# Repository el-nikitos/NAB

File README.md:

NAB

NAB_A - измерительный модуль-передатчик
NAB_B - модуль отображение-приемник
NAB_C - зарядная станция

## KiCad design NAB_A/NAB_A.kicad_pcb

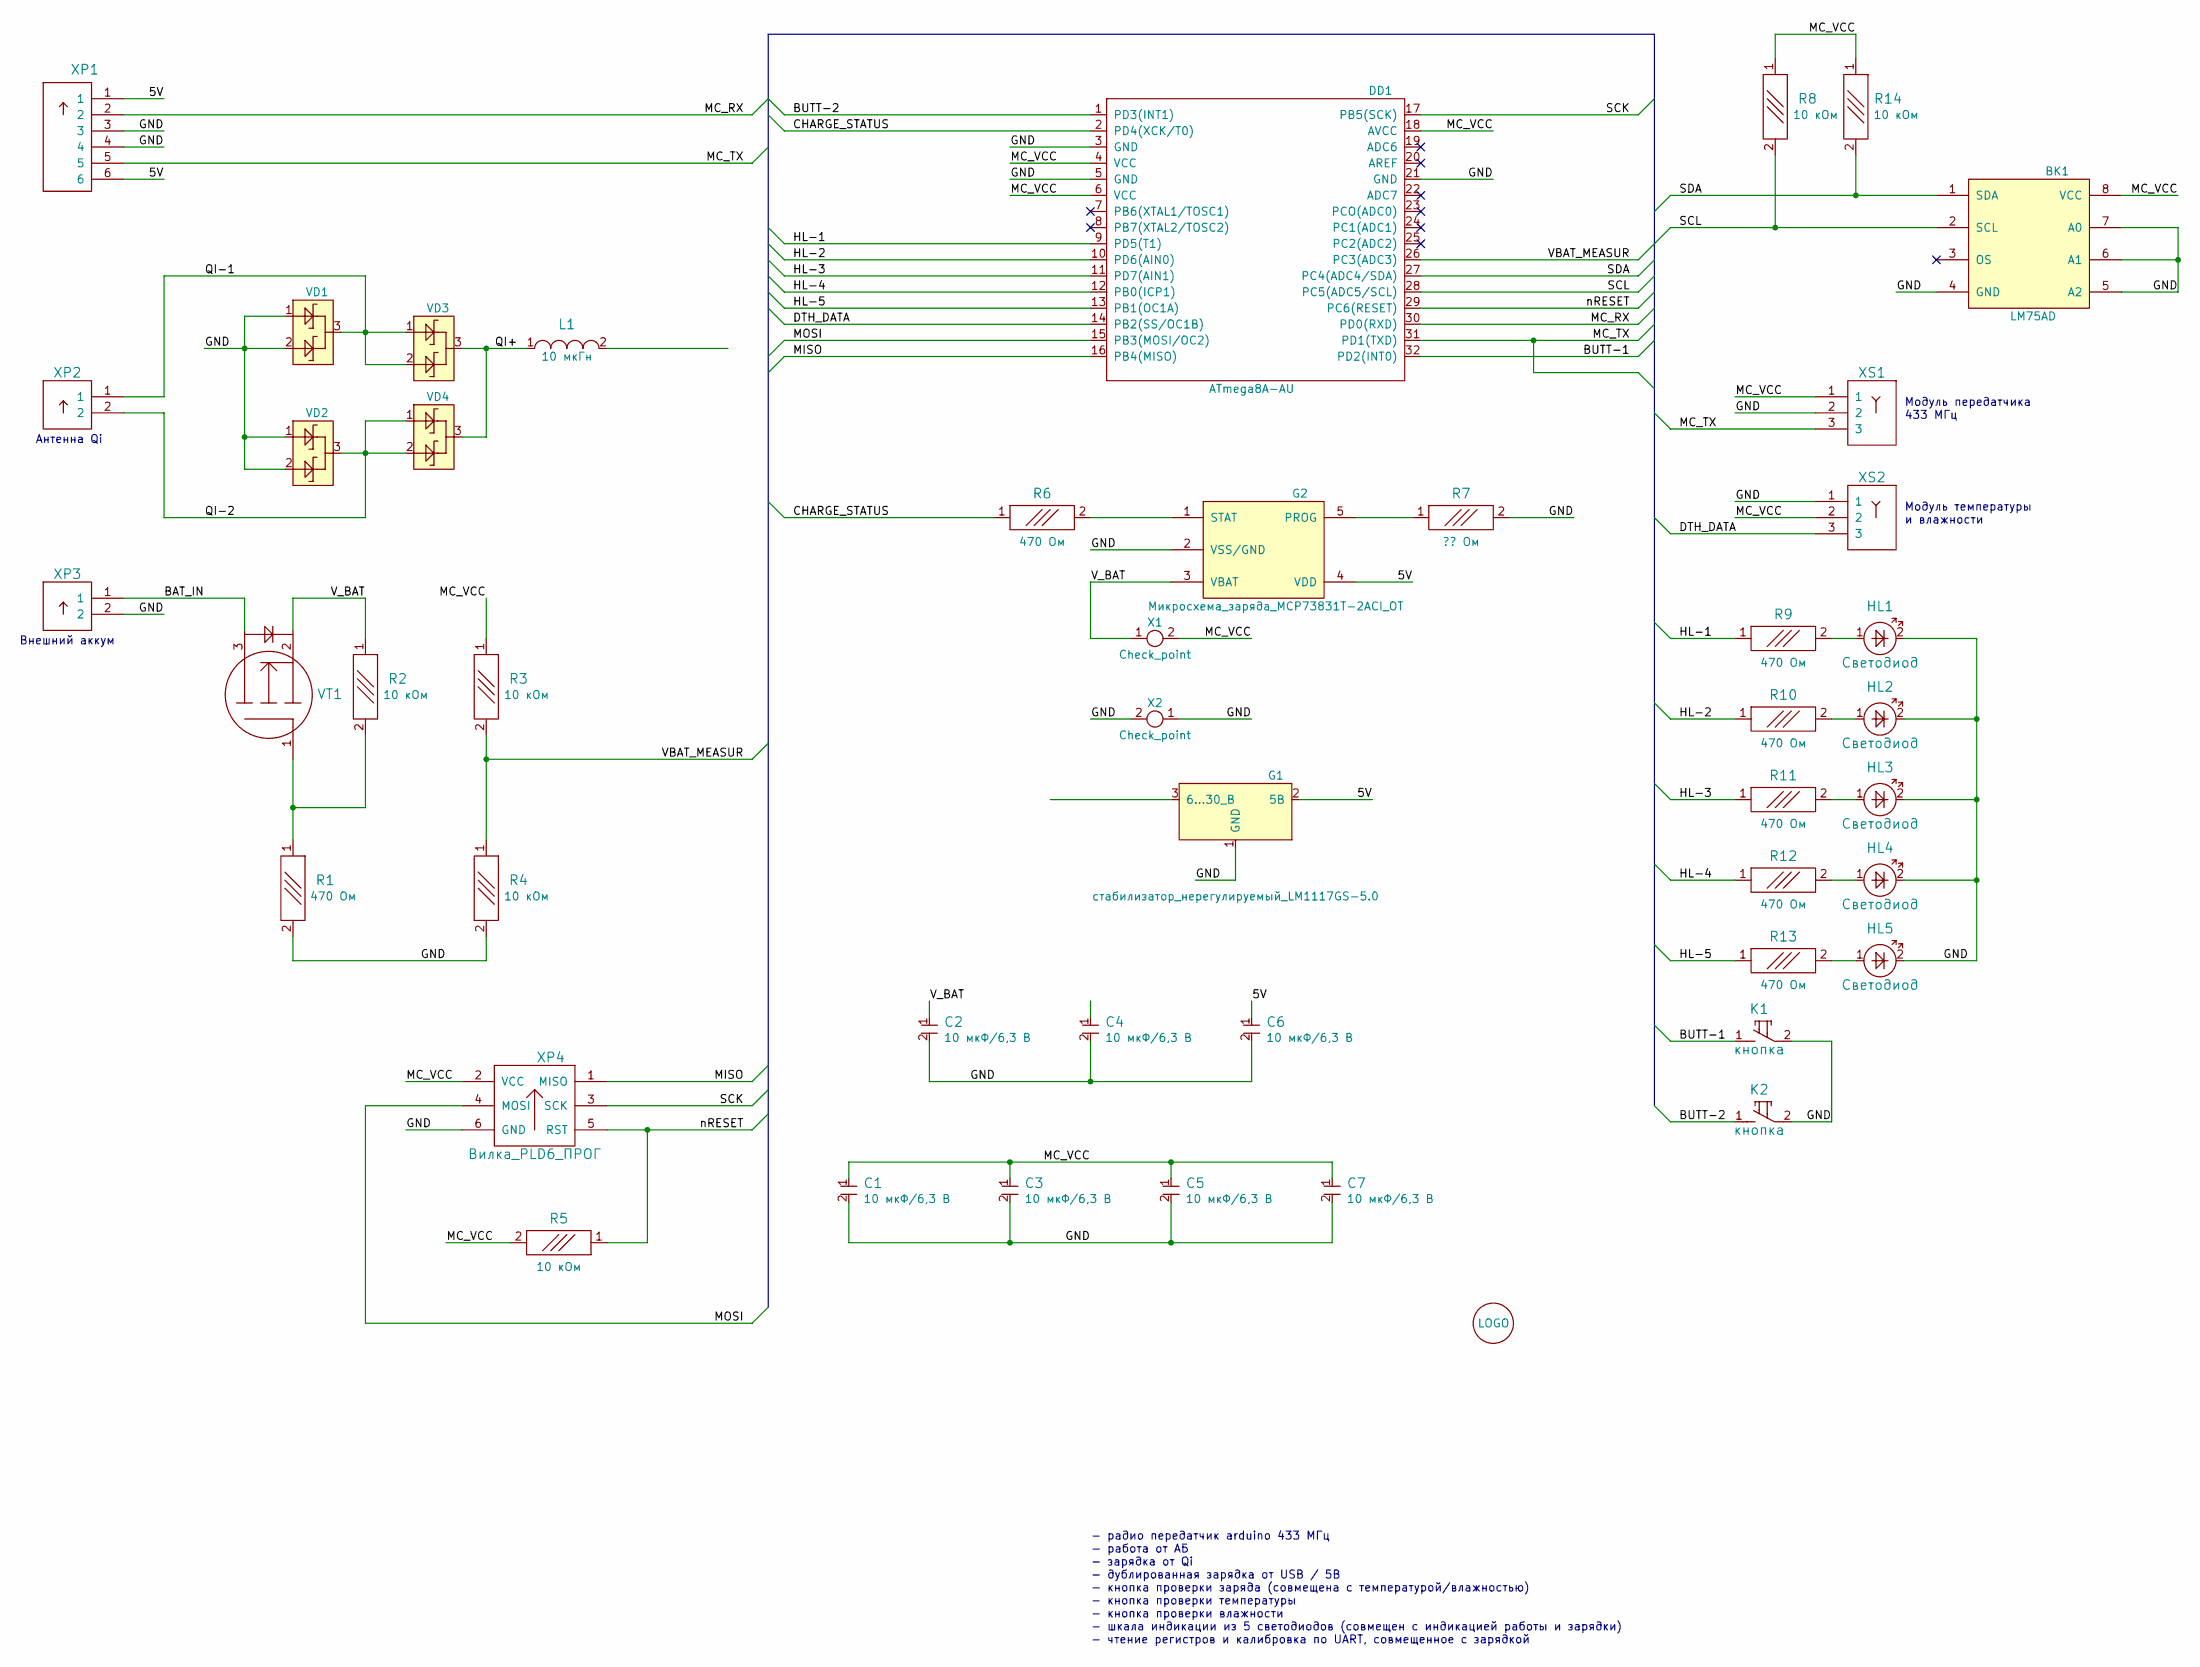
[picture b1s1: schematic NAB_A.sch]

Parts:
BK1: Преобразователь_температуры_LM75AD; SO-8
C1, C2, C3, C4, C5, C6, C7: Конденсатор_керамический; Конденсатор_SMD_0805
DD1: ATmega8A-AU; микросхема_ATMEGA-8-161AU
G1: стабилизатор_нерегулируемый_LM1117GS-5.0; Транзистор_NPN_SOT223
G2: Микросхема_заряда_MCP73831T-2ACI_OT; SC-70-5
HL1, HL2, HL3, HL4, HL5: Светодиод; Светодиод_SMD_0603
K1, K2: кнопка; Кнопка_FSMSM
L1: Чип-индуктивность_CM322522-100KL; Чип-индуктивность_SMD_1210
LOGO1: LOGO; ni_10x10
R1, R2, R3, R4, R5, R6, R7, R8, R9, R10, R11, R12, R13, R14: Резистор_0,065Вт; Резистор_SMD_0603_0,065_Вт
VD1, VD2, VD3, VD4: Диоды_шоттки_BAR43CFILM; Транзистор_IRLML6344TR_SOT-23
VT1: Транзистор_полевой_P-канал(IRLML2246TRPBF); Транзистор_IRLML6344TR_SOT-23
X1, X2: Check_point; Пробник
XP1: Вилка_PLS6; Вилка_PLS6_вертикальная
XP2, XP3: Вилка_PLS2; Вилка_PLS2_вертикальная
XP4: Вилка_PLD6_ПРОГ; Вилка_PLLD6_угловая_вертикальная
XS1, XS2: Розетка_PBS3; Розетка_PBS3_вертикальная

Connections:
/: C4.1, G1.3 (6...30_В), L1.2
/5V: C6.1, G1.2 (5В), G2.4 (VDD), XP1.1, XP1.6
/BAT_IN: VT1.3, XP3.1
/BUTT-1: DD1.32 (PD2(INT0)), K1.1
/BUTT-2: DD1.1 (PD3(INT1)), K2.1
/CHARGE_STATUS: DD1.2 (PD4(XCK/T0)), R6.1
/DTH_DATA: DD1.14 (PB2(SS/OC1B)), XS2.3
/GND: BK1.4 (GND), BK1.5 (A2), BK1.6 (A1), BK1.7 (A0), C1.2, C2.2, C3.2, C4.2, C5.2, C6.2, C7.2, DD1.3 (GND), DD1.5 (GND), DD1.21 (GND), G1.1 (GND), G2.2 (VSS/GND), HL1.2, HL2.2, HL3.2, HL4.2, HL5.2, K1.2, K2.2, R1.2, R4.2, R7.2, VD1.1, VD1.2, VD2.1, VD2.2, X2.1, X2.2, XP1.3, XP1.4, XP3.2, XP4.6 (GND), XS1.2, XS2.1
/HL-1: DD1.9 (PD5(T1)), R9.1
/HL-2: DD1.10 (PD6(AIN0)), R10.1
/HL-3: DD1.11 (PD7(AIN1)), R11.1
/HL-4: DD1.12 (PB0(ICP1)), R12.1
/HL-5: DD1.13 (PB1(OC1A)), R13.1
/MC_RX: DD1.30 (PD0(RXD)), XP1.2
/MC_TX: DD1.31 (PD1(TXD)), XP1.5, XS1.3
/MC_VCC: BK1.8 (VCC), C1.1, C3.1, C5.1, C7.1, DD1.4 (VCC), DD1.6 (VCC), DD1.18 (AVCC), R3.1, R5.2, R8.1, R14.1, X1.2, XP4.2 (VCC), XS1.1, XS2.2
/MISO: DD1.16 (PB4(MISO)), XP4.1 (MISO)
/MOSI: DD1.15 (PB3(MOSI/OC2)), XP4.4 (MOSI)
/QI+: L1.1, VD3.3, VD4.3
/QI-1: VD1.3, VD3.1, VD3.2, XP2.1
/QI-2: VD2.3, VD4.1, VD4.2, XP2.2
/SCK: DD1.17 (PB5(SCK)), XP4.3 (SCK)
/SCL: BK1.2 (SCL), DD1.28 (PC5(ADC5/SCL)), R8.2
/SDA: BK1.1 (SDA), DD1.27 (PC4(ADC4/SDA)), R14.2
/VBAT_MEASUR: DD1.26 (PC3(ADC3)), R3.2, R4.1
/V_BAT: C2.1, G2.3 (VBAT), R2.1, VT1.2, X1.1
/nRESET: DD1.29 (PC6(RESET)), R5.1, XP4.5 (RST)
unnamed: G2.1 (STAT), R6.2
unnamed: G2.5 (PROG), R7.1
unnamed: HL1.1, R9.2
unnamed: HL2.1, R10.2
unnamed: HL3.1, R11.2
unnamed: HL4.1, R12.2
unnamed: HL5.1, R13.2
unnamed: R1.1, R2.2, VT1.1

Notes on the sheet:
- радио передатчик arduino 433 МГц - работа от АБ - зарядка от Qi - дублированная зарядка от USB / 5В - кнопка проверки заряда (совмещена с температурой/влажностью) - кнопка проверки температуры - кнопка проверки влажности - шкала индикации из 5 светодиодов (совмещен с индикацией работы и зарядки) 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
Модуль передатчика 433 МГц
Модуль температуры и влажности
Антенна Qi
Внешний аккум

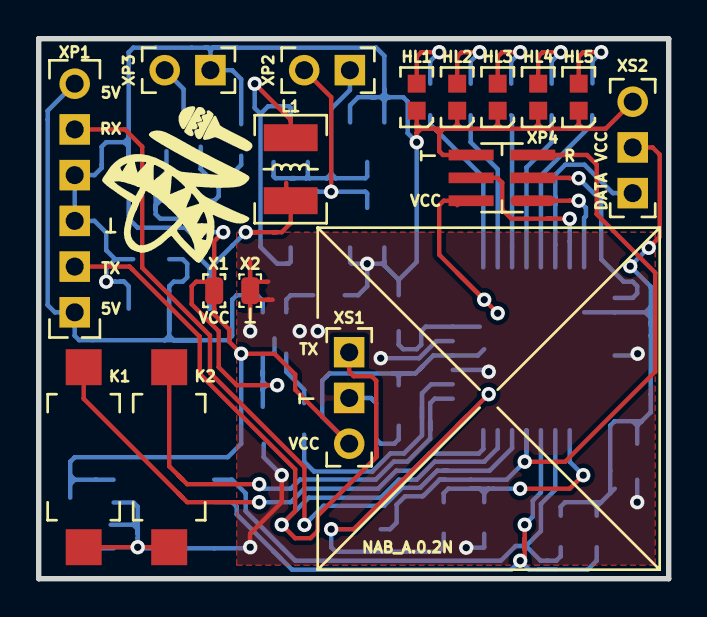
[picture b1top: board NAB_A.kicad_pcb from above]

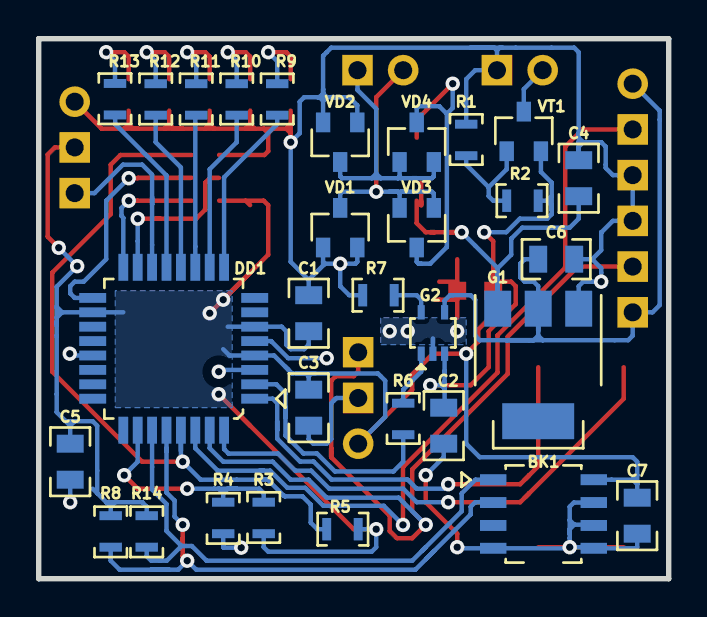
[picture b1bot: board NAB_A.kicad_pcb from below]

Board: 2 copper layers, 35.0 x 30.0 mm, 47 parts (30 on the bottom side), 35 nets.

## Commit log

2021-02-06 NAB_A: рыба схемы, определен предварительный габарит
2021-02-07 NAB_A: готова трассировка, требуется проверка и дополнить трассировку
2021-02-08 NAB_A: добавить оцифровку заряда, NAB_B: прототип взят от _A
2021-02-09 NAB_A: 433data перенесен на uart-tx, заведена аналоговая часть, +silk
2021-02-09 NAB_B: сформированы требования к плате
2021-02-16 NAB_A: добавлен ID на плату, подготовлены GERBER
